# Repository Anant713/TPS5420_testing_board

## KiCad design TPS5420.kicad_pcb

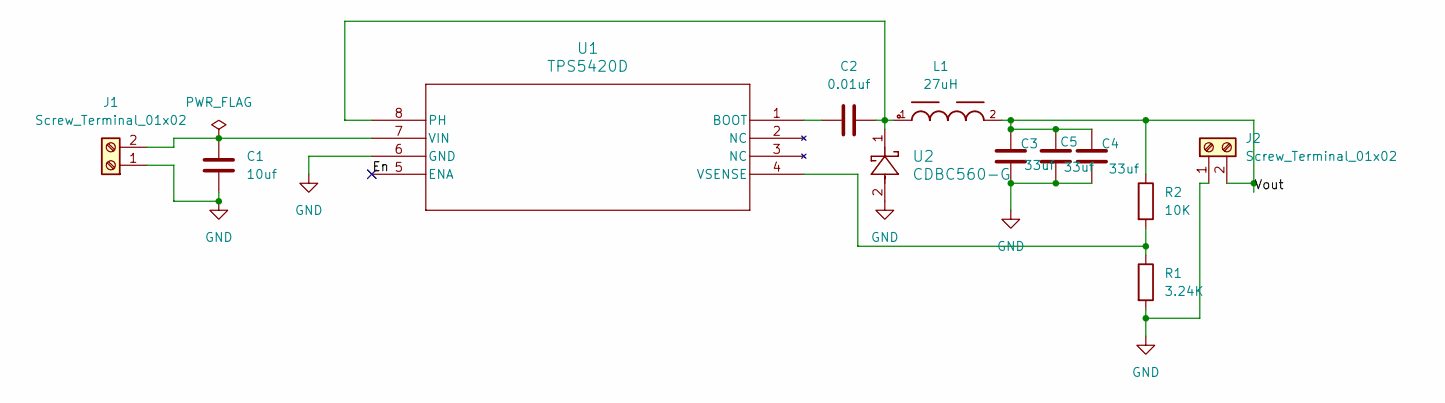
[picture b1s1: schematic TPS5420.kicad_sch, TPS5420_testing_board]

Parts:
C1: 10uf; C_1206_3216Metric_Pad1.33x1.80mm_HandSolder
C2: 0.01uf; C_1206_3216Metric_Pad1.33x1.80mm_HandSolder
C3, C4, C5: 33uf; C_1206_3216Metric_Pad1.33x1.80mm_HandSolder
J1, J2: Screw_Terminal_01x02; TerminalBlock_RND_205-00232_1x02_P5.08mm_Horizontal
L1: 27uH; WE-XHMI_5050
R1: 3.24K; 0805
R2: 10K; 0805
U1: TPS5420D; D8
U2: CDBC560-G; CDBC-G

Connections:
/En: U1.5 (ENA)
/Vout: C3.1, C4.1, C5.1, J2.2, L1.2, R2.1
GND: C1.2, C3.2, C4.2, C5.2, J1.1, J2.1, R1.2, U1.6 (GND), U2.2
unnamed: C1.1, J1.2, U1.7 (VIN)
unnamed: C2.1, U1.1 (BOOT)
unnamed: C2.2, L1.1, U1.8 (PH), U2.1
unnamed: R1.1, R2.2, U1.4 (VSENSE)

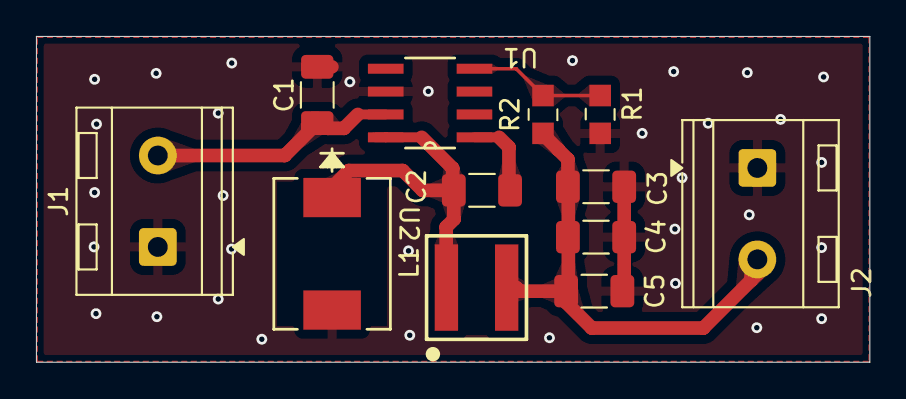
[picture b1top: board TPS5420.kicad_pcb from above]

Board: 2 copper layers, 46.3 x 18.1 mm, 12 parts (0 on the bottom side), 6 nets.

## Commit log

2025-11-20 SHifted out capacitors
2025-11-20 Added scre terminals
2025-11-20 v-03 Added ground pour and vias
2025-11-20 v01 - added ground pour
2025-11-20 v04 - Added stitching vias
